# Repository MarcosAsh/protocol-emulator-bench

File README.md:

# protocol-emulator bench

The carrier board for the [protocol-emulator](https://github.com/MarcosAsh/protocol-emulator) demo bench.
An Icepi Zero (ECP5) plays the chip and two Raspberry Pi Picos drive and check it. The board wires
them to every outside part the demos use: two CAN transceivers, an I2C EEPROM, a DS18B20, SPI flash,
a NeoPixel stick, SWD into the second Pico, 10BASE-T and two logic analysers.

v1.2, 100 x 100 mm, two layers, all through-hole, 47 nets, DRC clean. JLCPCB made and assembled it in
October 2026. The main repo's `demo/carrier_check.sh` tests every net it can reach on an assembled
board.

## Files

| Path | What |
|---|---|
| `carrier/gen.py` | builds the whole board from its parts and nets tables, then routes, checks and plots it |
| `carrier/carrier.kicad_pcb` | the board, KiCad 9 |
| `carrier/netlist.csv`, `carrier/bom.csv` | nets by pad, and the parts list with what you plug in yourself |
| `carrier/carrier_jlcpcb_gerbers.zip` | gerbers and drills, as ordered |
| `carrier/jlcpcb/` | JLC assembly BOM and placement files as ordered, and the note on what you fit after delivery |
| `carrier/renders/` | top and bottom renders and each layer |

## Ordering one

Upload `carrier_jlcpcb_gerbers.zip` to JLCPCB, then `jlcpcb/jlc_bom.csv` and `jlcpcb/jlc_cpl.csv` for
through-hole assembly. Check pin 1 of J1, J13-J16, U3, U4 and U5 in their placement preview.
`jlcpcb/assembly_note.txt` lists the boards and parts that plug in afterwards.

## Rebuilding

Needs KiCad 9 and its Python module on Linux. From `carrier/`, `python3 gen.py` rebuilds everything and
keeps the saved routing while placement and nets are unchanged. `python3 gen.py --reroute` routes again
with Freerouting, which it expects at `tools/freerouting.jar`.

## Licence

CERN-OHL-P v2, see `LICENSE`.

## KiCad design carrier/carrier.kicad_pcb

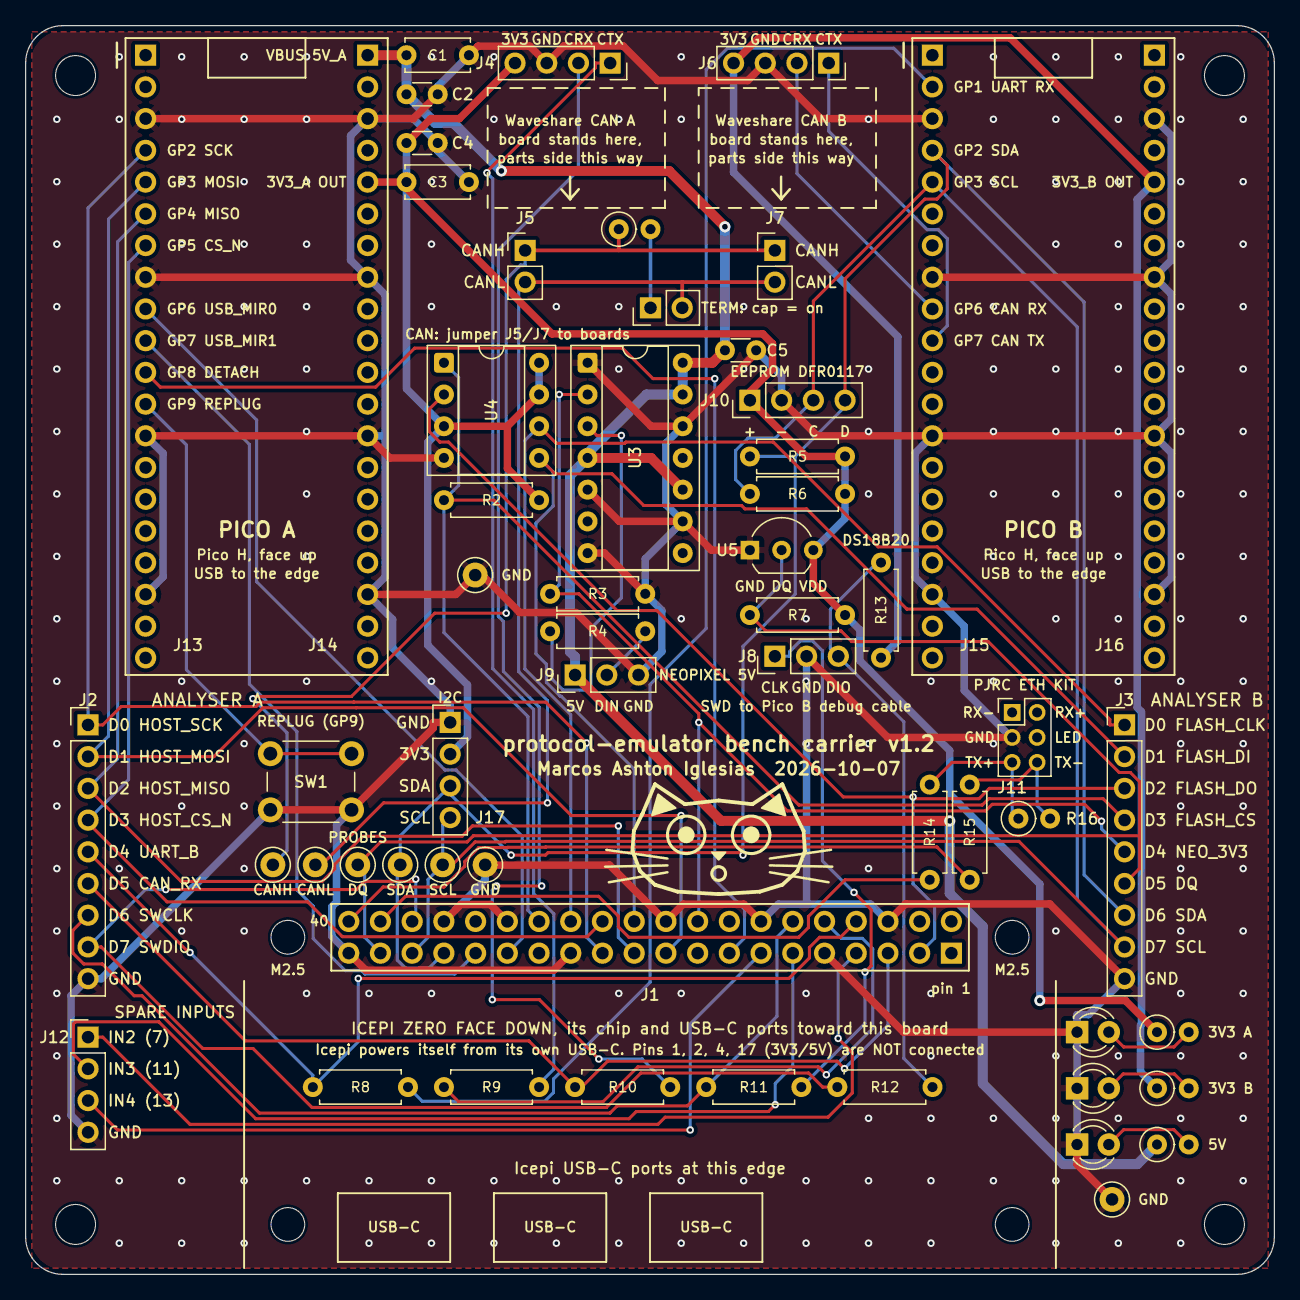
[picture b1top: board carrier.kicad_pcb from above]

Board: 2 copper layers, 100.0 x 100.0 mm, 65 parts (0 on the bottom side), 47 nets.

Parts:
C1, C3: 10u; C_Disc_D5.0mm_W2.5mm_P5.00mm
C2, C4, C5: 100n; C_Disc_D3.0mm_W1.6mm_P2.50mm
D1, D2: green; LED_D3.0mm
D3: red; LED_D3.0mm
H1, H2, H3, H4: M3; MountingHole_3.2mm_M3
H5, H6, H7, H8: M2.5; MountingHole_2.7mm_M2.5
J1: Icepi Zero; IcepiZero_Socket_2x20_FaceDown
J2: ANALYSER A; PinHeader_1x09_P2.54mm_Vertical
J3: ANALYSER B; PinHeader_1x09_P2.54mm_Vertical
J4: CAN A; PinSocket_1x04_P2.54mm_Vertical
J5: CAN A BUS; PinHeader_1x02_P2.54mm_Vertical
J6: CAN B; PinSocket_1x04_P2.54mm_Vertical
J7: CAN B BUS; PinHeader_1x02_P2.54mm_Vertical
J8: SWD; PinHeader_1x03_P2.54mm_Vertical
J9: NEOPIXEL; PinHeader_1x03_P2.54mm_Vertical
J10: EEPROM; PinHeader_1x04_P2.54mm_Vertical
J11: ETHERNET; PinHeader_2x03_P2.00mm_Vertical
J12: SPARE; PinHeader_1x04_P2.54mm_Vertical
J13: Pico A left; PinSocket_1x20_P2.54mm_Vertical_NoSilk
J14: Pico A right; PinSocket_1x20_P2.54mm_Vertical_NoSilk
J15: Pico B left; PinSocket_1x20_P2.54mm_Vertical_NoSilk
J16: Pico B right; PinSocket_1x20_P2.54mm_Vertical_NoSilk
J17: I2C; PinHeader_1x04_P2.54mm_Vertical
JP1: TERM; PinHeader_1x02_P2.54mm_Vertical
R1: 120R; R_Axial_DIN0207_L6.3mm_D2.5mm_P2.54mm_Vertical
R2, R3: 10k; R_Axial_DIN0207_L6.3mm_D2.5mm_P7.62mm_Horizontal
R4: 330R; R_Axial_DIN0207_L6.3mm_D2.5mm_P7.62mm_Horizontal
R5, R6: 2k2; R_Axial_DIN0207_L6.3mm_D2.5mm_P7.62mm_Horizontal
R7, R13: 4k7; R_Axial_DIN0207_L6.3mm_D2.5mm_P7.62mm_Horizontal
R8, R9, R10: 1k; R_Axial_DIN0207_L6.3mm_D2.5mm_P7.62mm_Horizontal
R11, R12: 220R; R_Axial_DIN0207_L6.3mm_D2.5mm_P7.62mm_Horizontal
R14, R15: 47R; R_Axial_DIN0207_L6.3mm_D2.5mm_P7.62mm_Horizontal
R16: 470R; R_Axial_DIN0207_L6.3mm_D2.5mm_P2.54mm_Vertical
R17, R18, R19: 1k; R_Axial_DIN0207_L6.3mm_D2.5mm_P2.54mm_Vertical
SW1: REPLUG; SW_PUSH_6mm
TP1, TP2, TP3: GND; TestPoint_Keystone_5000-5004_Miniature
TP4: CANH; TestPoint_Keystone_5000-5004_Miniature
TP5: CANL; TestPoint_Keystone_5000-5004_Miniature
TP6: DQ; TestPoint_Keystone_5000-5004_Miniature
TP7: SDA; TestPoint_Keystone_5000-5004_Miniature
TP8: SCL; TestPoint_Keystone_5000-5004_Miniature
U3: 74AHCT125; DIP-14_W7.62mm_Socket
U4: W25Q64 breakout; DIP-8_W7.62mm_Socket
U5: DS18B20; TO-92_Inline_Wide

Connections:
3V3_A: C3.1, C4.1, J4.4, J10.1, J14.5, J17.2, R2.2, R5.2, R6.2, R7.2, R17.1, U4.3, U4.7, U4.8, U5.3
3V3_B: J6.4, J16.5, R13.2, R18.1
5V_A: C1.1, C2.1, C5.1, J9.1, J14.1, R19.1, U3.4, U3.10, U3.13, U3.14
CANA_CRX: J4.2, R10.2
CANA_CTX: J4.1, R9.2
CANB_RX: J6.2, J15.9
CANB_TX: J6.1, J15.10
CANH: J5.1, J7.1, R1.1, TP4.1
CANL: J5.2, J7.2, JP1.2, TP5.1
CAN_RX: J1.5, J2.6, R10.1
CAN_TERM: JP1.1, R1.2
CAN_TX: J1.10, R9.1
DQ: J1.37, J3.6, R7.1, TP6.1, U5.2
ETH_TXN: J1.40, R15.1
ETH_TXN_J: J11.6, R15.2, R16.2
ETH_TXP: J1.38, R14.1
ETH_TXP_J: J11.5, R14.2, R16.1
FLASH_CLK: J1.26, J3.1, U4.6
FLASH_CS_N: J1.28, J3.4, R2.1, U4.1
FLASH_DI: J1.22, J3.2, U4.5
FLASH_DO: J1.3, J3.3, U4.2
GND: C1.2, C2.2, C3.2, C4.2, C5.2, D1.1, D2.1, D3.1, J1.6, J1.9, J1.14, J1.20, J1.25, J1.30, J1.34, J1.39, J2.9, J3.9, J4.3, J6.3, J8.2, J9.3, J10.2, J11.3, J12.4, J13.3, J13.8, J13.13, J13.18, J14.3, J14.8, J14.13, J14.18, J15.3, J15.8, J15.13, J15.18, J16.3, J16.8, J16.13, J16.18, J17.1, R3.2, SW1.2, TP1.1, TP2.1, TP3.1, U3.1, U3.5, U3.7, U3.9, U3.12, U4.4, U5.1
HOST_CS_N: J1.24, J2.4, J13.7
HOST_MISO: J1.21, J2.3, J13.6
HOST_MOSI: J1.19, J2.2, J13.5
HOST_SCK: J1.23, J2.1, J13.4
I2C_SCL: J1.35, J3.8, J10.3, J15.5, J17.4, R6.1, TP8.1
I2C_SDA: J1.33, J3.7, J10.4, J15.4, J17.3, R5.1, TP7.1
LED_3V3A: D1.2, R17.2
LED_3V3B: D2.2, R18.2
LED_5V: D3.2, R19.2
NEO_3V3: J1.18, J3.5, R3.1, U3.2
NEO_5V: R4.1, U3.3
NEO_DIN: J9.2, R4.2
REPLUG: J13.12, SW1.1
SPARE_IN2: J1.7, J12.1
SPARE_IN3: J1.11, J12.2
SPARE_IN4: J1.13, J12.3
SWCLK: J1.12, J2.7, R11.1
SWCLK_PICO: J8.1, R11.2
SWDIO: J1.36, J2.8, R12.1
SWDIO_PICO: J8.3, R12.2, R13.1
UART_B: J1.8, J2.5, R8.1
UART_B_PICO: J15.2, R8.2
USB_DETACH: J1.15, J13.11
USB_MIR0: J1.29, J13.9
USB_MIR1: J1.31, J13.10

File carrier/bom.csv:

qty,refs,value,description,part number,footprint,fit
1,C1,10u,"5V_A bulk, leaded MLCC 10 uF 25 V X5R, 5.08 mm",Dersonic CD1E106MC9BER2F100,Capacitor_THT:C_Disc_D5.0mm_W2.5mm_P5.00mm,fit
1,C2,100n,5V_A decoupling,Fenghua CT4-0805B104K500F1,Capacitor_THT:C_Disc_D3.0mm_W1.6mm_P2.50mm,fit
1,C3,10u,"3V3_A bulk, leaded MLCC 10 uF 25 V X5R, 5.08 mm",Dersonic CD1E106MC9BER2F100,Capacitor_THT:C_Disc_D5.0mm_W2.5mm_P5.00mm,fit
1,C4,100n,3V3_A decoupling,Fenghua CT4-0805B104K500F1,Capacitor_THT:C_Disc_D3.0mm_W1.6mm_P2.50mm,fit
1,C5,100n,74AHCT125 VCC decoupling,Fenghua CT4-0805B104K500F1,Capacitor_THT:C_Disc_D3.0mm_W1.6mm_P2.50mm,fit
1,D1,green,"3 mm green LED, 3V3_A on",Everlight 204-10SYGD/S530-E2-L,LED_THT:LED_D3.0mm,fit
1,D2,green,"3 mm green LED, 3V3_B on",Everlight 204-10SYGD/S530-E2-L,LED_THT:LED_D3.0mm,fit
1,D3,red,"3 mm red LED, 5V_A on",Everlight 204-10SDRD/S530-A3-L,LED_THT:LED_D3.0mm,fit
1,J1,Icepi Zero,"2x20 female header 2.54 mm, 8.5 mm tall (Icepi Zero socket)",Sullins PPTC202LFBN-RC,carrier:icepi,fit
1,J10,EEPROM,1x4 male header 2.54 mm (Gravity cable dupont ends),generic 2.54 mm break-away header,Connector_PinHeader_2.54mm:PinHeader_1x04_P2.54mm_Vertical,fit
1,J11,ETHERNET,2x3 male header 2.00 mm (PJRC kit ribbon cable),Sullins NRPN032PAEN-RC,Connector_PinHeader_2.00mm:PinHeader_2x03_P2.00mm_Vertical,fit
1,J12,SPARE,1x4 male header 2.54 mm,generic 2.54 mm break-away header,Connector_PinHeader_2.54mm:PinHeader_1x04_P2.54mm_Vertical,fit
1,J13,Pico A left,"1x20 female header 2.54 mm, 8.5 mm (Pico A pins 1-20)",Kinghelm KH-2.54FH-1X20P-H8.5,Connector_PinSocket_2.54mm:PinSocket_1x20_P2.54mm_Vertical,fit
1,J14,Pico A right,"1x20 female header 2.54 mm, 8.5 mm (Pico A pins 40-21)",Kinghelm KH-2.54FH-1X20P-H8.5,Connector_PinSocket_2.54mm:PinSocket_1x20_P2.54mm_Vertical,fit
1,J15,Pico B left,"1x20 female header 2.54 mm, 8.5 mm (Pico B pins 1-20)",Kinghelm KH-2.54FH-1X20P-H8.5,Connector_PinSocket_2.54mm:PinSocket_1x20_P2.54mm_Vertical,fit
1,J16,Pico B right,"1x20 female header 2.54 mm, 8.5 mm (Pico B pins 40-21)",Kinghelm KH-2.54FH-1X20P-H8.5,Connector_PinSocket_2.54mm:PinSocket_1x20_P2.54mm_Vertical,fit
1,J17,I2C,"1x4 male header 2.54 mm, spare I2C (GND 3V3 SDA SCL)",generic 2.54 mm break-away header,Connector_PinHeader_2.54mm:PinHeader_1x04_P2.54mm_Vertical,fit
1,J2,ANALYSER A,1x9 male header 2.54 mm,generic 2.54 mm break-away header,Connector_PinHeader_2.54mm:PinHeader_1x09_P2.54mm_Vertical,fit
1,J3,ANALYSER B,1x9 male header 2.54 mm,generic 2.54 mm break-away header,Connector_PinHeader_2.54mm:PinHeader_1x09_P2.54mm_Vertical,fit
1,J4,CAN A,1x4 female header 2.54 mm (Waveshare SN65HVD230 board A),Sullins PPTC041LFBN-RC,Connector_PinSocket_2.54mm:PinSocket_1x04_P2.54mm_Vertical,fit
1,J5,CAN A BUS,1x2 male header 2.54 mm (CANH/CANL jumpers to board A),generic 2.54 mm break-away header,Connector_PinHeader_2.54mm:PinHeader_1x02_P2.54mm_Vertical,fit
1,J6,CAN B,1x4 female header 2.54 mm (Waveshare SN65HVD230 board B),Sullins PPTC041LFBN-RC,Connector_PinSocket_2.54mm:PinSocket_1x04_P2.54mm_Vertical,fit
1,J7,CAN B BUS,1x2 male header 2.54 mm (CANH/CANL jumpers to board B),generic 2.54 mm break-away header,Connector_PinHeader_2.54mm:PinHeader_1x02_P2.54mm_Vertical,fit
1,J8,SWD,1x3 male header 2.54 mm (Pico debug cable jumper ends),generic 2.54 mm break-away header,Connector_PinHeader_2.54mm:PinHeader_1x03_P2.54mm_Vertical,fit
1,J9,NEOPIXEL,1x3 male header 2.54 mm,generic 2.54 mm break-away header,Connector_PinHeader_2.54mm:PinHeader_1x03_P2.54mm_Vertical,fit
1,JP1,TERM,1x2 male header 2.54 mm (CAN terminator on/off) + shunt,generic 2.54 mm header + jumper cap,Connector_PinHeader_2.54mm:PinHeader_1x02_P2.54mm_Vertical,fit
1,R1,120R,"resistor, 1/4 W metal film 1 %",Yageo MFR-25FBF52-120R,Resistor_THT:R_Axial_DIN0207_L6.3mm_D2.5mm_P2.54mm_Vertical,fit
2,R11 R12,220R,"resistor, 1/4 W metal film 1 %",Yageo MFR-25FBF52-220R,Resistor_THT:R_Axial_DIN0207_L6.3mm_D2.5mm_P7.62mm_Horizontal,fit
2,R14 R15,47R,"resistor, 1/4 W metal film 1 %",Yageo MFR-25FBF52-47R,Resistor_THT:R_Axial_DIN0207_L6.3mm_D2.5mm_P7.62mm_Horizontal,fit
1,R16,470R,"resistor, 1/4 W metal film 1 %",Yageo MFR-25FBF52-470R,Resistor_THT:R_Axial_DIN0207_L6.3mm_D2.5mm_P2.54mm_Vertical,fit
3,R17 R18 R19,1k,"resistor, 1/4 W metal film 1 %",Yageo MFR-25FBF52-1K,Resistor_THT:R_Axial_DIN0207_L6.3mm_D2.5mm_P2.54mm_Vertical,fit
2,R2 R3,10k,"resistor, 1/4 W metal film 1 %",Yageo MFR-25FBF52-10K,Resistor_THT:R_Axial_DIN0207_L6.3mm_D2.5mm_P7.62mm_Horizontal,fit
1,R4,330R,"resistor, 1/4 W metal film 1 %",Yageo MFR-25FBF52-330R,Resistor_THT:R_Axial_DIN0207_L6.3mm_D2.5mm_P7.62mm_Horizontal,fit
2,R5 R6,2k2,"resistor, 1/4 W metal film 1 %",Yageo MFR-25FBF52-2K2,Resistor_THT:R_Axial_DIN0207_L6.3mm_D2.5mm_P7.62mm_Horizontal,fit
2,R7 R13,4k7,"resistor, 1/4 W metal film 1 %",Yageo MFR-25FBF52-4K7,Resistor_THT:R_Axial_DIN0207_L6.3mm_D2.5mm_P7.62mm_Horizontal,fit
3,R8 R9 R10,1k,"resistor, 1/4 W metal film 1 %",Yageo MFR-25FBF52-1K,Resistor_THT:R_Axial_DIN0207_L6.3mm_D2.5mm_P7.62mm_Horizontal,fit
1,SW1,REPLUG,"6 mm THT tactile switch, Pico A GP9 to GND",HRO K2-1102DP-C4SW-04,Button_Switch_THT:SW_PUSH_6mm,fit
3,TP1 TP2 TP3,GND,"test loop GND, black",Keystone 5001,TestPoint:TestPoint_Keystone_5000-5004_Miniature,fit
1,TP4,CANH,"test loop, white",Keystone 5002,TestPoint:TestPoint_Keystone_5000-5004_Miniature,fit
1,TP5,CANL,"test loop, white",Keystone 5002,TestPoint:TestPoint_Keystone_5000-5004_Miniature,fit
1,TP6,DQ,"test loop, white",Keystone 5002,TestPoint:TestPoint_Keystone_5000-5004_Miniature,fit
1,TP7,SDA,"test loop, white",Keystone 5002,TestPoint:TestPoint_Keystone_5000-5004_Miniature,fit
1,TP8,SCL,"test loop, white",Keystone 5002,TestPoint:TestPoint_Keystone_5000-5004_Miniature,fit
1,U3,74AHCT125,"quad buffer, 5 V, DIP-14 (+ DIP-14 socket)",TI SN74AHCT125N + Mill-Max 110-43-314-41-001000,Package_DIP:DIP-14_W7.62mm_Socket,fit
1,U4,W25Q64 breakout,Adafruit QSPI DIP breakout W25Q64 (+ DIP-8 socket),Adafruit 5633 + Mill-Max 110-43-308-41-001000,Package_DIP:DIP-8_W7.62mm_Socket,fit
1,U5,DS18B20,"1-Wire temperature sensor, TO-92",Analog Devices DS18B20+,Package_TO_SOT_THT:TO-92_Inline_Wide,fit

qty,plug-in,value,description,part number,,
1,J1,Icepi Zero,ECP5 FPGA board playing the chip (v1.3/v1.4),cheyao Icepi Zero (Elecrow),,
2,U1 U2,Pico H,"Raspberry Pi Pico H, headers fitted",Raspberry Pi SC0917,,
2,J4 J6,CAN board,Waveshare SN65HVD230 CAN Board,Waveshare SKU 3945,,
1,U4,flash,Adafruit QSPI DIP breakout W25Q64,Adafruit 5633,,
1,J10,EEPROM,DFRobot Gravity 24LC256 I2C EEPROM module + Gravity-to-dupont cable,DFRobot DFR0117,,
1,J11,MagJack,PJRC Ethernet Kit for Teensy 4.1 (with its ribbon cable),PJRC ETHERNET_KIT,,
1,JP1,shunt,2.54 mm jumper cap for the CAN terminator (cap on = terminated),BOOMELE C100114,,
4,H1-H4,M3,M3 standoff + screw (corners),generic,,
4,H5-H8,M2.5,"optional M2.5 standoffs under the Icepi, height = socket stack",generic,,
